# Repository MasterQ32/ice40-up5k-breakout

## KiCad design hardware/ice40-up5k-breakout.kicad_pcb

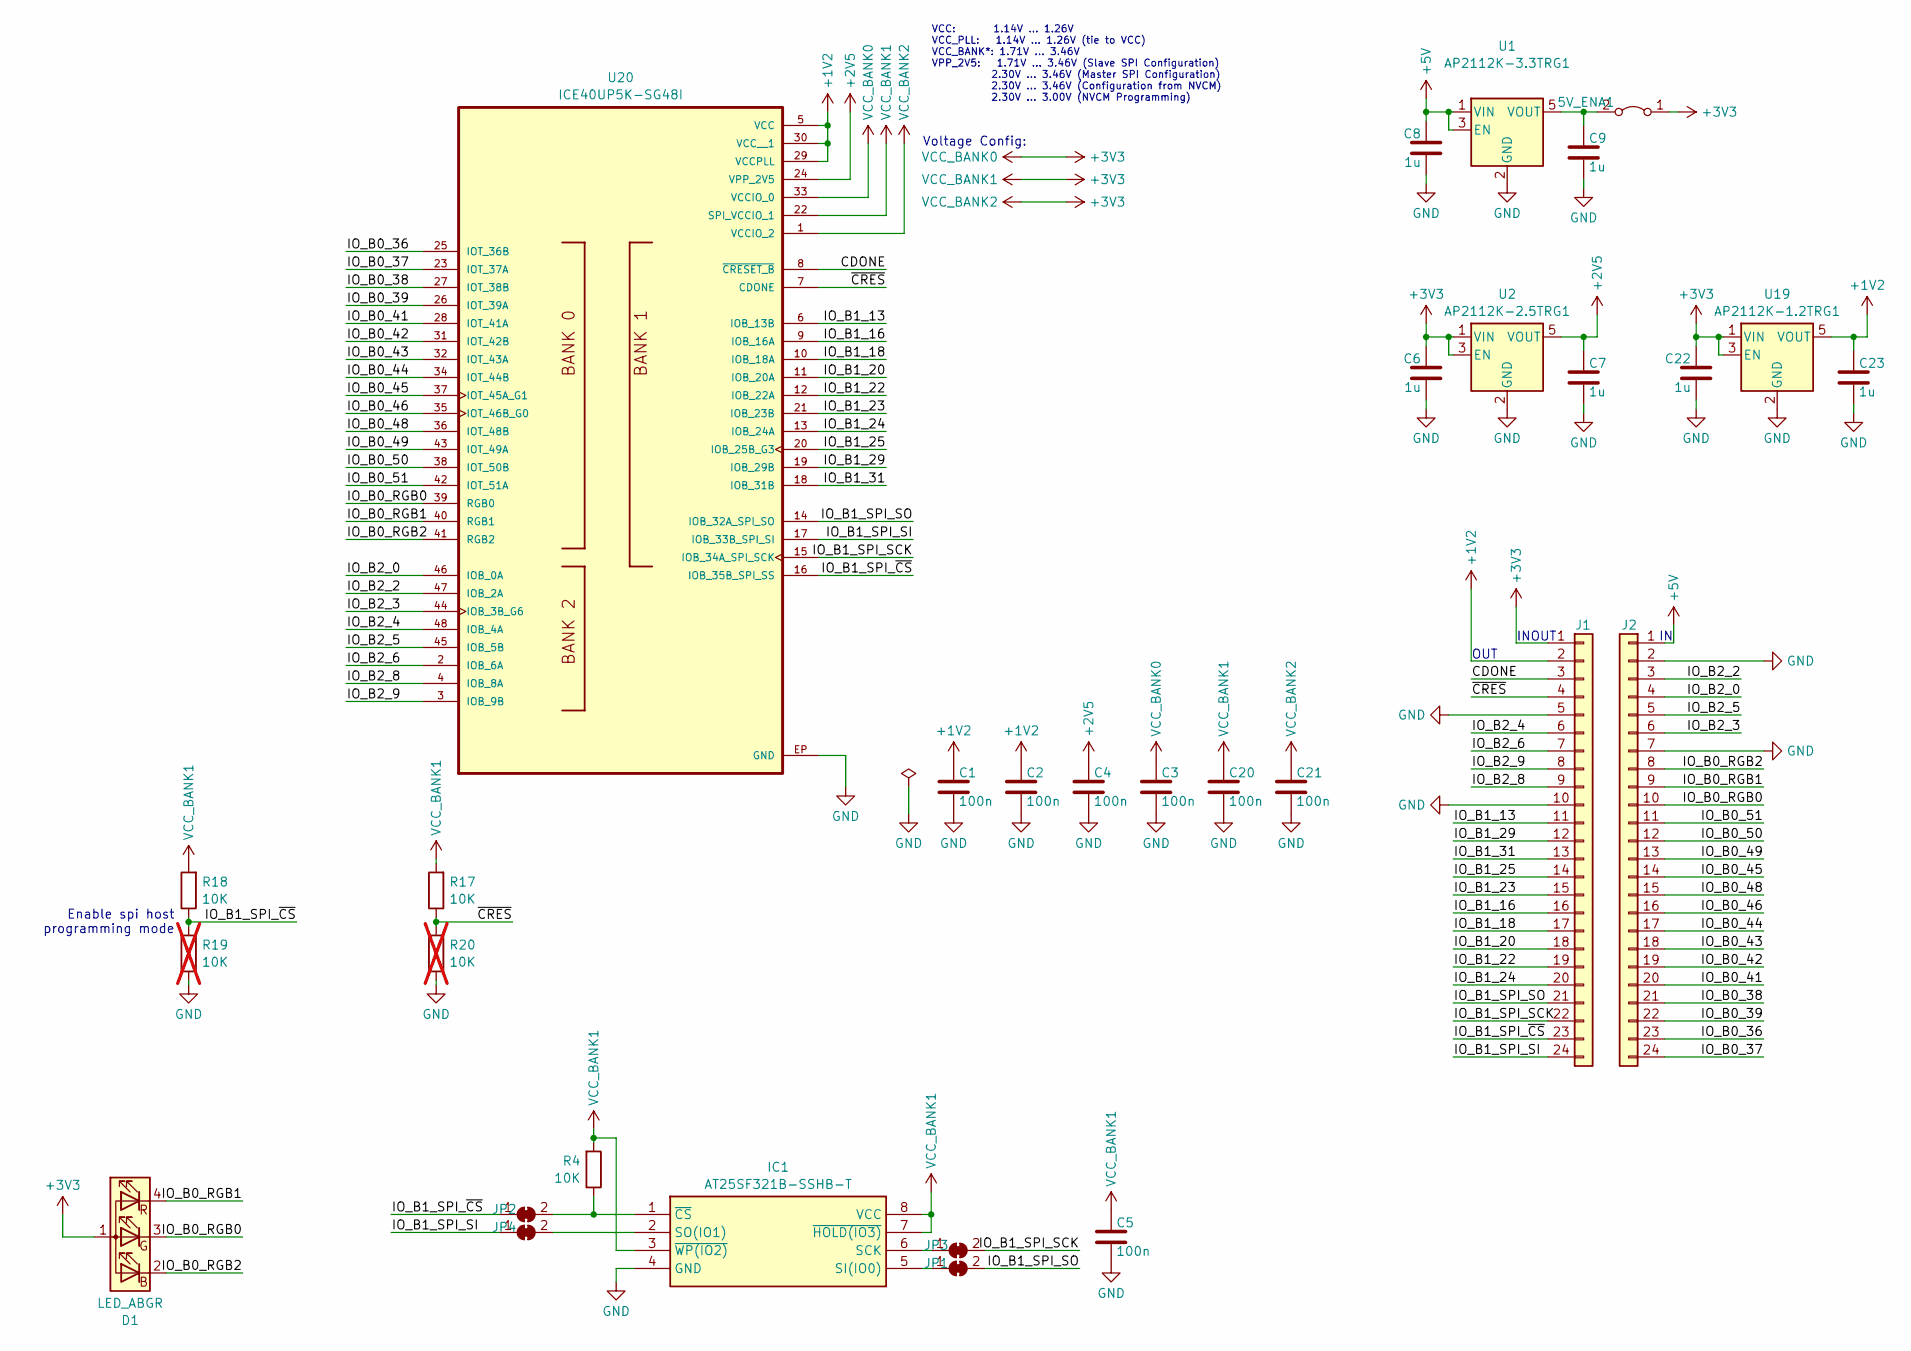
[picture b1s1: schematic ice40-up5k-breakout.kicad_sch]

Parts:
5V_ENA1: Jumper_2_Bridged; PinHeader_1x02_P2.54mm_Horizontal
C1, C2, C3, C4, C5, C20, C21: 100n; C_0603_1608Metric_Pad1.08x0.95mm_HandSolder
C6, C7, C8, C9, C22, C23: 1u; C_0603_1608Metric_Pad1.08x0.95mm_HandSolder
D1: LED_ABGR; LED_RGB_1210
IC1: AT25SF321B-SSHB-T; at25sf321b; DigiKey Part No. 1265-AT25SF321B-SSHB-TCT-ND
J1, J2: Conn_01x24; PinHeader_1x24_P2.54mm_Vertical
JP1, JP2, JP3, JP4: SolderJumper_2_Bridged; SolderJumper-2_P1.3mm_Open_RoundedPad1.0x1.5mm
R4, R17, R18: 10K; R_0603_1608Metric_Pad0.98x0.95mm_HandSolder
R19, R20: 10K; R_0603_1608Metric_Pad0.98x0.95mm_HandSolder; not fitted
U1: AP2112K-3.3TRG1; AP2112K-3_3TRG1; DigiKey Part No. AP2112K-3.3TRG1DICT-ND
U2: AP2112K-2.5TRG1; AP2112K-2_5TRG1; DigiKey Part No. 31-AP2112K-2.5TRG1CT-ND
U19: AP2112K-1.2TRG1; AP2112K-1_2TRG1; DigiKey Part No. 31-AP2112K-1.2TRG1CT-ND
U20: ICE40UP5K-SG48I; DigiKey Part No. 220-2212-1-ND

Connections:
+1V2: C1.1, C2.1, C23.1, J1.2, U19.5 (VOUT), U20.5 (VCC), U20.29 (VCCPLL), U20.30 (VCC__1)
+2V5: C4.1, C7.1, U2.5 (VOUT), U20.24 (VPP_2V5)
+3V3: 5V_ENA1.1 (A), C3.1, C5.1, C6.1, C20.1, C21.1, C22.1, D1.1 (A), IC1.3 (~WP(IO2)), IC1.7 (~HOLD(IO3)), IC1.8 (VCC), J1.1, R4.2, R17.2, R18.2, U2.1 (VIN), U2.3 (EN), U19.1 (VIN), U19.3 (EN), U20.1 (VCCIO_2), U20.22 (SPI_VCCIO_1), U20.33 (VCCIO_0)
+5V: C8.1, J2.1, U1.1 (VIN), U1.3 (EN)
/CDONE: J1.3, U20.8 (~CRESET_B)
/IO_B0_36: J2.23, U20.25 (IOT_36B)
/IO_B0_37: J2.24, U20.23 (IOT_37A)
/IO_B0_38: J2.21, U20.27 (IOT_38B)
/IO_B0_39: J2.22, U20.26 (IOT_39A)
/IO_B0_41: J2.20, U20.28 (IOT_41A)
/IO_B0_42: J2.19, U20.31 (IOT_42B)
/IO_B0_43: J2.18, U20.32 (IOT_43A)
/IO_B0_44: J2.17, U20.34 (IOT_44B)
/IO_B0_45: J2.14, U20.37 (IOT_45A_G1)
/IO_B0_46: J2.16, U20.35 (IOT_46B_G0)
/IO_B0_48: J2.15, U20.36 (IOT_48B)
/IO_B0_49: J2.13, U20.43 (IOT_49A)
/IO_B0_50: J2.12, U20.38 (IOT_50B)
/IO_B0_51: J2.11, U20.42 (IOT_51A)
/IO_B0_RGB0: D1.3 (GK), J2.10, U20.39 (RGB0)
/IO_B0_RGB1: D1.4 (RK), J2.9, U20.40 (RGB1)
/IO_B0_RGB2: D1.2 (BK), J2.8, U20.41 (RGB2)
/IO_B1_13: J1.11, U20.6 (IOB_13B)
/IO_B1_16: J1.16, U20.9 (IOB_16A)
/IO_B1_18: J1.17, U20.10 (IOB_18A)
/IO_B1_20: J1.18, U20.11 (IOB_20A)
/IO_B1_22: J1.19, U20.12 (IOB_22A)
/IO_B1_23: J1.15, U20.21 (IOB_23B)
/IO_B1_24: J1.20, U20.13 (IOB_24A)
/IO_B1_25: J1.14, U20.20 (IOB_25B_G3)
/IO_B1_29: J1.12, U20.19 (IOB_29B)
/IO_B1_31: J1.13, U20.18 (IOB_31B)
/IO_B1_SPI_SCK: J1.22, JP3.2 (B), U20.15 (IOB_34A_SPI_SCK)
/IO_B1_SPI_SI: J1.24, JP4.1 (A), U20.17 (IOB_33B_SPI_SI)
/IO_B1_SPI_SO: J1.21, JP1.2 (B), U20.14 (IOB_32A_SPI_SO)
/IO_B1_SPI_~CS: J1.23, JP2.1 (A), R18.1, R19.2, U20.16 (IOB_35B_SPI_SS)
/IO_B2_0: J2.4, U20.46 (IOB_0A)
/IO_B2_2: J2.3, U20.47 (IOB_2A)
/IO_B2_3: J2.6, U20.44 (IOB_3B_G6)
/IO_B2_4: J1.6, U20.48 (IOB_4A)
/IO_B2_5: J2.5, U20.45 (IOB_5B)
/IO_B2_6: J1.7, U20.2 (IOB_6A)
/IO_B2_8: J1.9, U20.4 (IOB_8A)
/IO_B2_9: J1.8, U20.3 (IOB_9B)
/~CRES: J1.4, R17.1, R20.2, U20.7 (CDONE)
GND: C1.2, C2.2, C3.2, C4.2, C5.2, C6.2, C7.2, C8.2, C9.2, C20.2, C21.2, C22.2, C23.2, IC1.4 (GND), J1.5, J1.10, J2.2, J2.7, R19.1, R20.1, U1.2 (GND), U2.2 (GND), U19.2 (GND), U20.EP (GND)
unnamed: 5V_ENA1.2 (B), C9.1, U1.5 (VOUT)
unnamed: IC1.6 (SCK), JP3.1 (A)
unnamed: IC1.5 (SI(IO0)), JP1.1 (A)
unnamed: IC1.2 (SO(IO1)), JP4.2 (B)
unnamed: IC1.1 (~CS), JP2.2 (B), R4.1

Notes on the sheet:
Enable spi host programming mode
INOUT
OUT
Voltage Config:
VCC: 1.14V … 1.26V VCC_PLL: 1.14V … 1.26V (tie to VCC) VCC_BANK*: 1.71V … 3.46V VPP_2V5: 1.71V … 3.46V (Slave SPI Configuration) 2.30V … 3.46V (Master SPI Configuration) 2.30V … 3.46V (Configuration from NVCM) 2.30V … 3.00V (NVCM Programming)

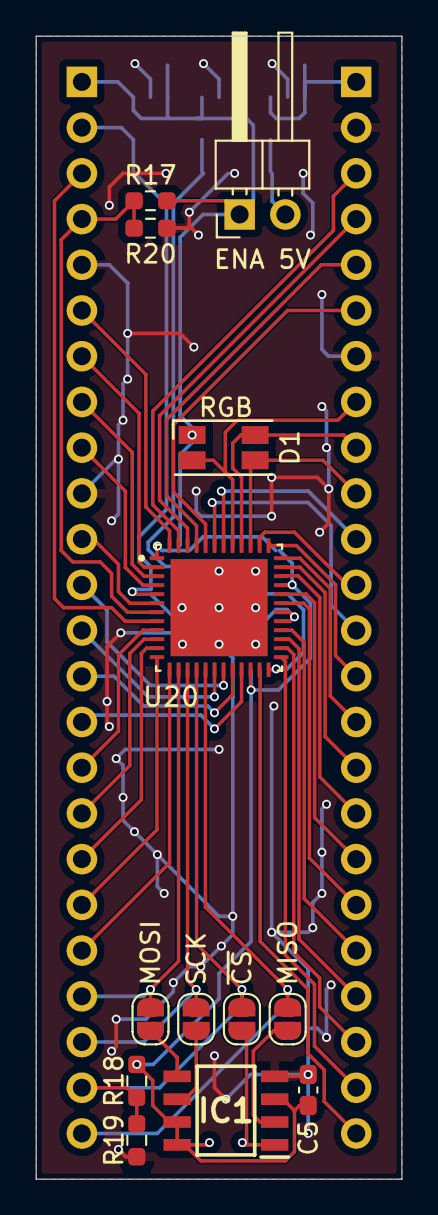
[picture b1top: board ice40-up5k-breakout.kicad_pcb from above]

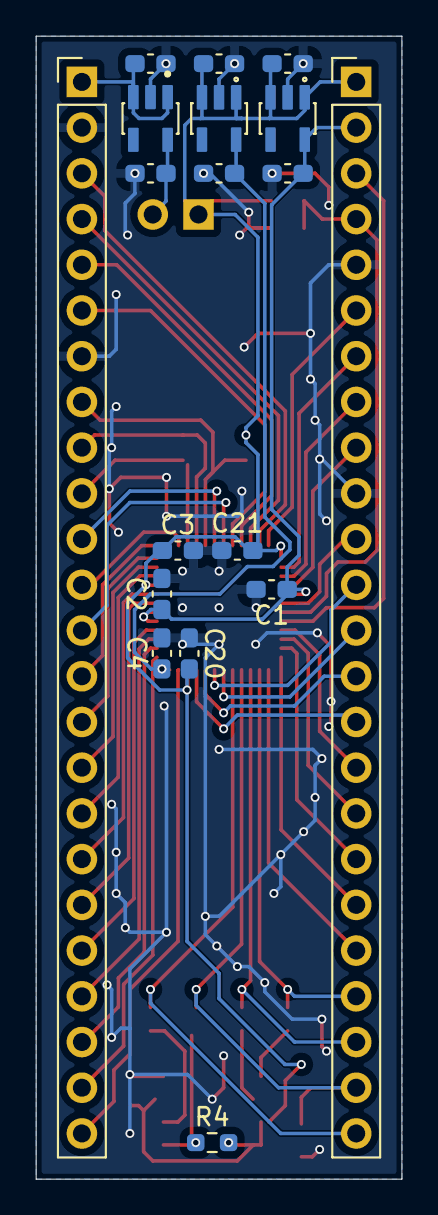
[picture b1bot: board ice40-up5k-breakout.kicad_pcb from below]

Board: 2 copper layers, 20.3 x 63.5 mm, 31 parts (18 on the bottom side), 51 nets.

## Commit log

2023-10-29 Initial commit: Basic two-layered board.
2023-10-30 Adds .gitignore
2023-10-30 Finalizes draft 1.
